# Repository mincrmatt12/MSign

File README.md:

# MSign

Code + designs for an LED sign display board powered by an STM32 and ESP8266. Make sure you clone the submodules.

## Organization

- `board`: schematics and PCB layout
- `stm`: STM32 firmware (drives the display)
- `stmboot`: STM32 bootloader
- `esp`: ESP8266 firmware (grabs information from the internet)
- `espweb`: ESP8266 web-based configuration page source
- `cfgserver`: Server for shipping unattended config and software updates (without using the webui)
- `bmap`: Tools for generating graphics resources
- `caplog`: Tools for debugging
- `vendor`: Various dependencies in source form (everything not listed below)
- `sim`: Stubs/shims for running the `esp` and `stm` codebases under linux.

## Dependencies

- A recent `arm-none-eabi-gcc` installation (suitably modern to deal with C++20; GCC 14 is what's tested)
- A `xtensa-lx106-elf-gcc` that can deal with C++20; preferably version 13.2.0 (which was available at one point in debian)
  - A suitable newlib/libstdc++ archive is available in `Dockerfile.build`
- Python 3 and the packages in `requirements.txt`
  - If you aren't building the `espweb` directory you do not require the `cryptography` package listed
- OpenOCD (for flashing)
  - If you have PlatformIO installed we use its OpenOCD by default, so you may not need to install it system-wide.
- CMake (version 3.13 or later is recommended)
- `quilt`, to apply the patches in `vendor` for the ESP8266 SDK

and everything checked out in the `vendor` directory. The ESP8266 SDK also usually requests you have python (specifically _system_ python, whatever runs from `python`) installed with it's requirements (`vendor/ESP8266_RTOS_SDK/requirements.txt`)

A Docker file with these is provided as `Dockerfile.build`.

For building the `espweb` you also need:

- yarn
- node 

A Docker file with _these_ is also provided as `Dockerfile.webbuild`

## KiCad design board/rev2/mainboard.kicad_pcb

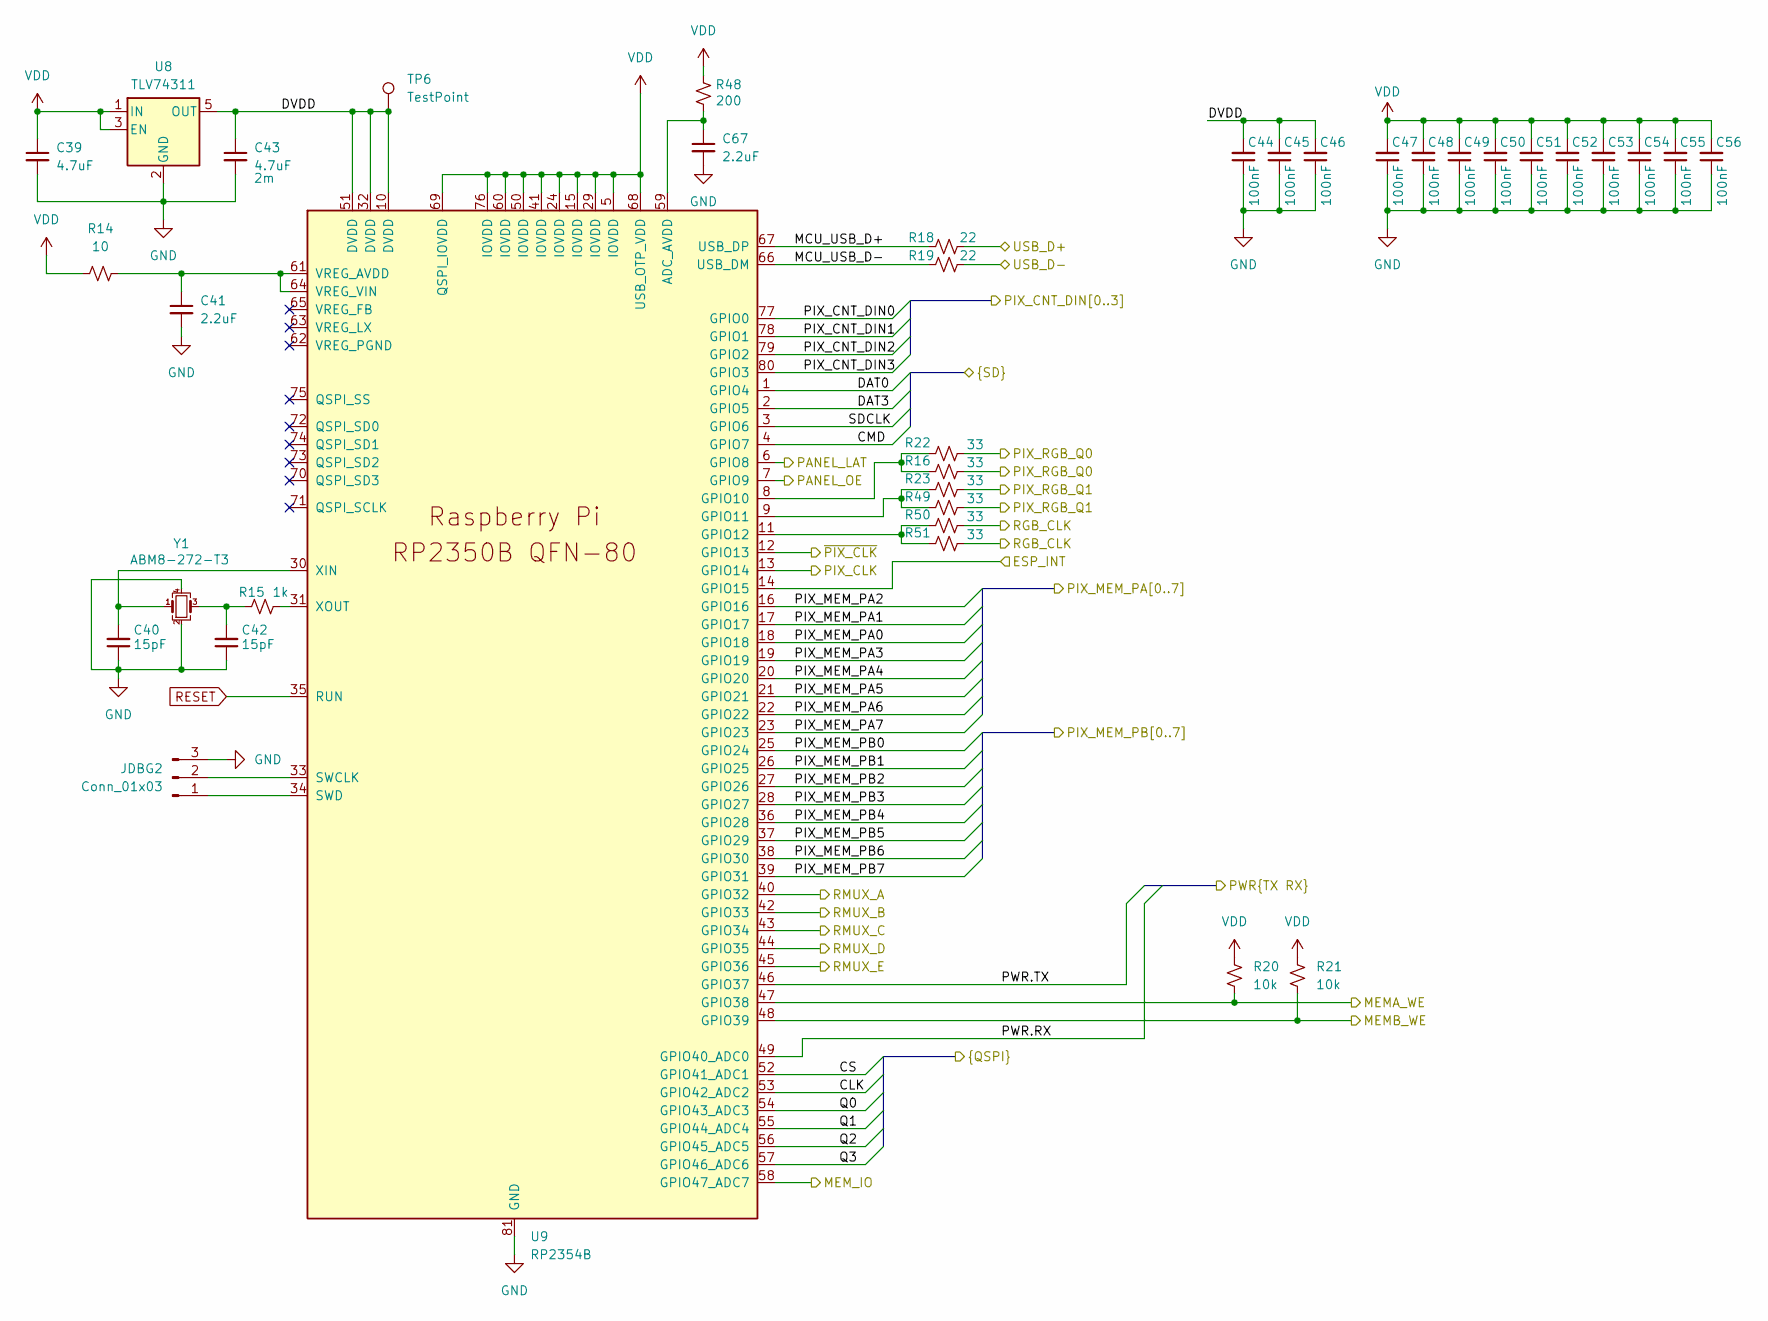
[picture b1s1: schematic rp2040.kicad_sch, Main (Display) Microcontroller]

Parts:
C39, C43: 4.7uF; C_1206_3216Metric; Part 1206B475K500NT; LCSC C29823
C40, C42: 15pF; C_0402_1005Metric; Part 0402CG150J500NT; LCSC C1548
C41, C67: 2.2uF; C_0603_1608Metric; Part CL10A225KO8NNNC; LCSC C23630
C44, C45, C46, C47, C48, C49, C50, C51, C52, C53, C54, C55, C56: 100nF; C_0402_1005Metric; Part CL05B104KB54PNC; LCSC C307331
JDBG2: Conn_01x03; PinHeader_1x03_P2.54mm_Vertical
R14: 10; R_0402_1005Metric; Part 0402WGF100JTCE; LCSC C25077
R15: 1k; R_0402_1005Metric; Part 0402WGF1001TCE; LCSC C11702
R16, R22, R23, R49, R50, R51: 33; R_0402_1005Metric; Part 0402WGF330JTCE; LCSC C25105
R18, R19: 22; R_0402_1005Metric; Part 0402WGF220JTCE; LCSC C25092
R20, R21: 10k; R_0402_1005Metric; Part 0402WGF1002TCE; LCSC C25744
R48: 200; R_0402_1005Metric; Part 0402WGF2000TCE; LCSC C25087
TP6: TestPoint; TestPoint_Pad_D1.0mm
U8: TLV74311; SOT-23-5; Part TLV74311PDBVR; LCSC C485147
U9: RP2354B; RP2350-QFN-80-1EP_10x10_P0.4mm_EP3.4x3.4mm_ThermalVias; Part RP2354B; LCSC C39843328
Y1: ABM8-272-T3; Crystal_SMD_3225-4Pin_3.2x2.5mm; Part ABM8-272-T3; LCSC C20625731

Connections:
/Decoder/MEMA_WE: R20.2, U9.47 (GPIO38); also elsewhere on the board
/Decoder/MEMB_WE: R21.2, U9.48 (GPIO39); also elsewhere on the board
/Decoder/MEM_IO: U9.58 (GPIO47_ADC7); also elsewhere on the board
/Decoder/Output Stage A/PIX_RGB_Q0: R16.2, R22.2; also elsewhere on the board
/Decoder/Output Stage A/PIX_RGB_Q1: R23.2, R49.2; also elsewhere on the board
/Decoder/PIX_CLK: U9.13 (GPIO14); also elsewhere on the board
/Decoder/PIX_CNT_DIN0: U9.77 (GPIO0); also elsewhere on the board
/Decoder/PIX_CNT_DIN1: U9.78 (GPIO1); also elsewhere on the board
/Decoder/PIX_CNT_DIN2: U9.79 (GPIO2); also elsewhere on the board
/Decoder/PIX_CNT_DIN3: U9.80 (GPIO3); also elsewhere on the board
/Decoder/PIX_MEM_PA0: U9.25 (GPIO24); also elsewhere on the board
/Decoder/PIX_MEM_PA1: U9.26 (GPIO25); also elsewhere on the board
/Decoder/PIX_MEM_PA2: U9.27 (GPIO26); also elsewhere on the board
/Decoder/PIX_MEM_PA3: U9.28 (GPIO27); also elsewhere on the board
/Decoder/PIX_MEM_PA4: U9.36 (GPIO28); also elsewhere on the board
/Decoder/PIX_MEM_PA5: U9.37 (GPIO29); also elsewhere on the board
/Decoder/PIX_MEM_PA6: U9.38 (GPIO30); also elsewhere on the board
/Decoder/PIX_MEM_PA7: U9.39 (GPIO31); also elsewhere on the board
/Decoder/PIX_MEM_PB0: U9.18 (GPIO18); also elsewhere on the board
/Decoder/PIX_MEM_PB1: U9.17 (GPIO17); also elsewhere on the board
/Decoder/PIX_MEM_PB2: U9.16 (GPIO16); also elsewhere on the board
/Decoder/PIX_MEM_PB3: U9.19 (GPIO19); also elsewhere on the board
/Decoder/PIX_MEM_PB4: U9.20 (GPIO20); also elsewhere on the board
/Decoder/PIX_MEM_PB5: U9.21 (GPIO21); also elsewhere on the board
/Decoder/PIX_MEM_PB6: U9.22 (GPIO22); also elsewhere on the board
/Decoder/PIX_MEM_PB7: U9.23 (GPIO23); also elsewhere on the board
/Decoder/RGB_CLK: R50.2, R51.2; also elsewhere on the board
/Display MCU/CLK: U9.53 (GPIO42_ADC2); also elsewhere on the board
/Display MCU/CMD: U9.4 (GPIO7); also elsewhere on the board
/Display MCU/CS: U9.52 (GPIO41_ADC1); also elsewhere on the board
/Display MCU/DAT0: U9.1 (GPIO4); also elsewhere on the board
/Display MCU/DAT3: U9.2 (GPIO5); also elsewhere on the board
/Display MCU/DVDD: C43.1, C44.2, C45.2, C46.2, TP6.1 (1_1), U8.5 (OUT), U9.10 (DVDD), U9.32 (DVDD), U9.51 (DVDD)
/Display MCU/ESP_INT: U9.14 (GPIO15); also elsewhere on the board
/Display MCU/MCU_USB_D+: R18.1, U9.67 (USB_DP)
/Display MCU/MCU_USB_D-: R19.1, U9.66 (USB_DM)
/Display MCU/PANEL_LAT: U9.6 (GPIO8); also elsewhere on the board
/Display MCU/PANEL_OE: U9.7 (GPIO9); also elsewhere on the board
/Display MCU/PWR.RX: U9.49 (GPIO40_ADC0); also elsewhere on the board
/Display MCU/PWR.TX: U9.46 (GPIO37); also elsewhere on the board
/Display MCU/Q0: U9.54 (GPIO43_ADC3); also elsewhere on the board
/Display MCU/Q1: U9.55 (GPIO44_ADC4); also elsewhere on the board
/Display MCU/Q2: U9.56 (GPIO45_ADC5); also elsewhere on the board
/Display MCU/Q3: U9.57 (GPIO46_ADC6); also elsewhere on the board
/Display MCU/RMUX_A: U9.40 (GPIO32); also elsewhere on the board
/Display MCU/RMUX_B: U9.42 (GPIO33); also elsewhere on the board
/Display MCU/RMUX_C: U9.43 (GPIO34); also elsewhere on the board
/Display MCU/RMUX_D: U9.44 (GPIO35); also elsewhere on the board
/Display MCU/RMUX_E: U9.45 (GPIO36); also elsewhere on the board
/Display MCU/SDCLK: U9.3 (GPIO6); also elsewhere on the board
/Display MCU/USB_D+: R18.2; also elsewhere on the board
/Display MCU/USB_D-: R19.2; also elsewhere on the board
/Display MCU/~PIX_CLK: U9.12 (GPIO13); also elsewhere on the board
GND: C39.2, C40.1, C41.2, C42.1, C43.2, C44.1, C45.1, C46.1, C47.1, C48.1, C49.1, C50.1, C51.1, C52.1, C53.1, C54.1, C55.1, C56.1, C67.2, JDBG2.3, U8.2 (GND), U9.81 (GND), Y1.2, Y1.4; also elsewhere on the board
unnamed: C42.2, R15.1, Y1.3
unnamed: JDBG2.1, U9.34 (SWD)
unnamed: JDBG2.2, U9.33 (SWCLK)
unnamed: C67.1, R48.2, U9.59 (ADC_AVDD)
unnamed: R16.1, R22.1, U9.8 (GPIO10)
unnamed: R23.1, R49.1, U9.9 (GPIO11)
unnamed: R50.1, R51.1, U9.11 (GPIO12)
unnamed: C41.1, R14.2, U9.61 (VREG_AVDD), U9.64 (VREG_VIN)
unnamed: C40.2, U9.30 (XIN), Y1.1
unnamed: R15.2, U9.31 (XOUT)
RESET: U9.35 (RUN); also elsewhere on the board
VDD: C39.1, C47.2, C48.2, C49.2, C50.2, C51.2, C52.2, C53.2, C54.2, C55.2, C56.2, R14.1, R20.1, R21.1, R48.1, U8.1 (IN), U8.3 (EN), U9.5 (IOVDD), U9.15 (IOVDD), U9.24 (IOVDD), U9.29 (IOVDD), U9.41 (IOVDD), U9.50 (IOVDD), U9.60 (IOVDD), U9.68 (USB_OTP_VDD), U9.69 (QSPI_IOVDD), U9.76 (IOVDD); also elsewhere on the board

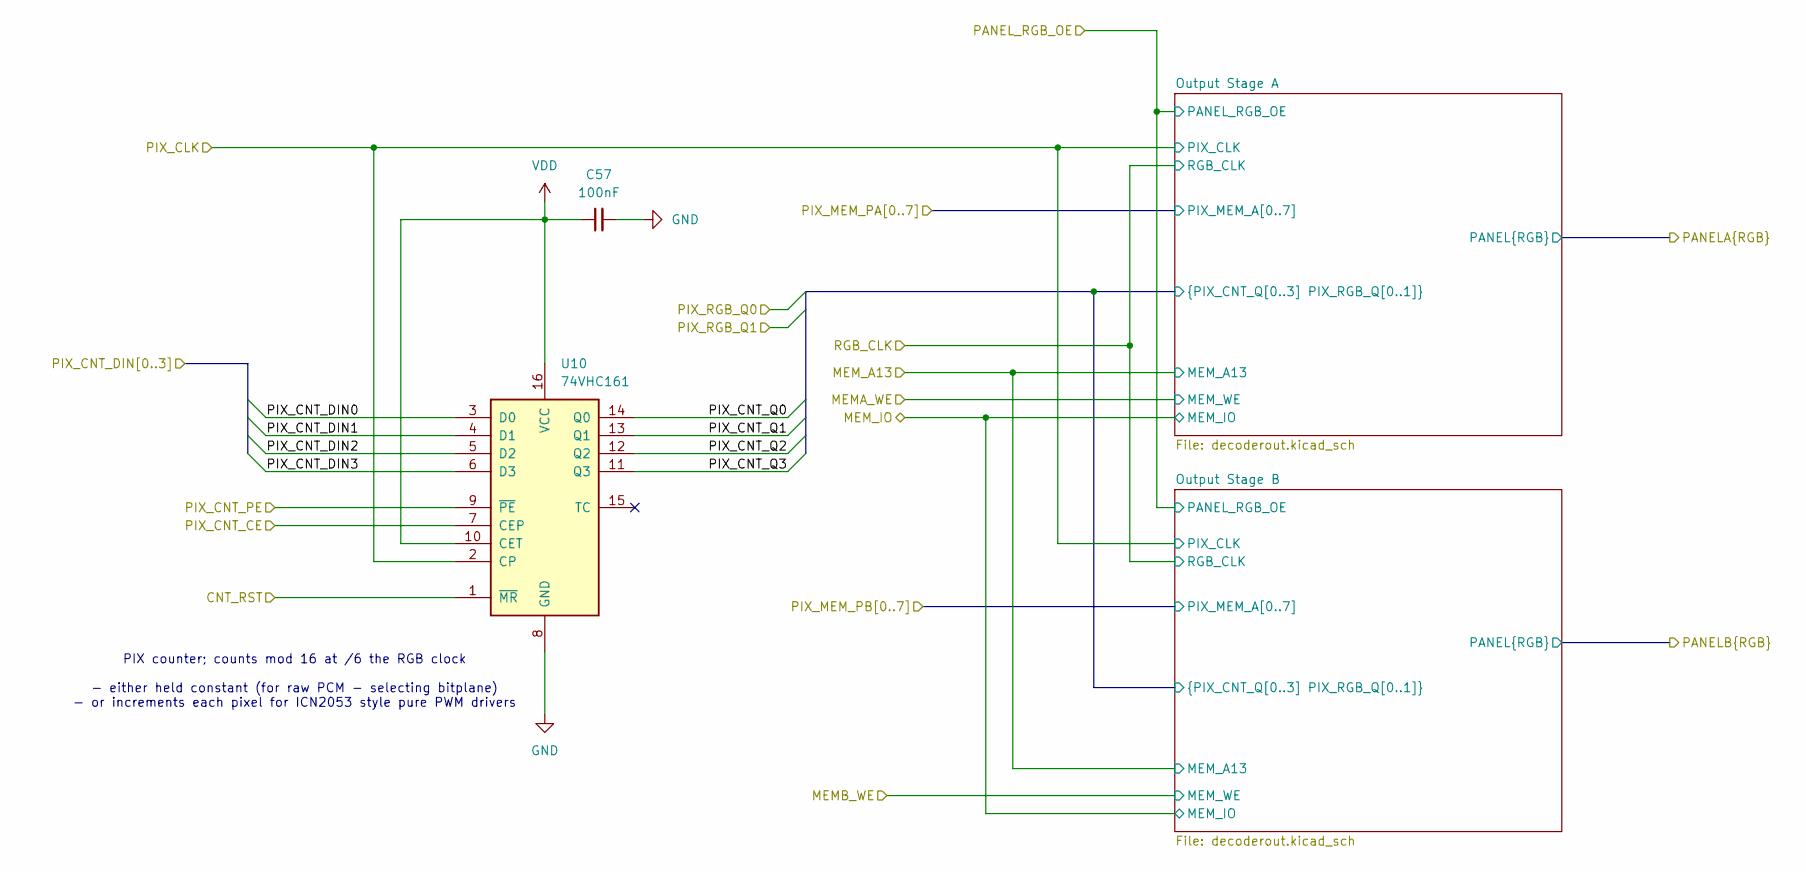
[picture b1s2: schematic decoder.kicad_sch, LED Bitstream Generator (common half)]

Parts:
C57: 100nF; C_0402_1005Metric; Part CL05B104KB54PNC; LCSC C307331
U10: 74VHC161; TSSOP-16_4.4x5mm_P0.65mm; Part 74VHC161FT(BJ); LCSC C7421276

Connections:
/Decoder/CNT_RST: U10.1 (~MR); also elsewhere on the board
/Decoder/Output Stage A/PIX_CNT_Q0: U10.14 (Q0); also elsewhere on the board
/Decoder/Output Stage A/PIX_CNT_Q1: U10.13 (Q1); also elsewhere on the board
/Decoder/Output Stage A/PIX_CNT_Q2: U10.12 (Q2); also elsewhere on the board
/Decoder/Output Stage A/PIX_CNT_Q3: U10.11 (Q3); also elsewhere on the board
/Decoder/PIX_CLK: U10.2 (CP); also elsewhere on the board
/Decoder/PIX_CNT_CE: U10.7 (CEP); also elsewhere on the board
/Decoder/PIX_CNT_DIN0: U10.3 (D0); also elsewhere on the board
/Decoder/PIX_CNT_DIN1: U10.4 (D1); also elsewhere on the board
/Decoder/PIX_CNT_DIN2: U10.5 (D2); also elsewhere on the board
/Decoder/PIX_CNT_DIN3: U10.6 (D3); also elsewhere on the board
/Decoder/PIX_CNT_PE: U10.9 (~PE); also elsewhere on the board
GND: C57.2, U10.8 (GND); also elsewhere on the board
VDD: C57.1, U10.10 (CET), U10.16 (VCC); also elsewhere on the board

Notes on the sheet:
PIX counter; counts mod 16 at /6 the RGB clock - either held constant (for raw PCM - selecting bitplane) - or increments each pixel for ICN2053 style pure PWM drivers

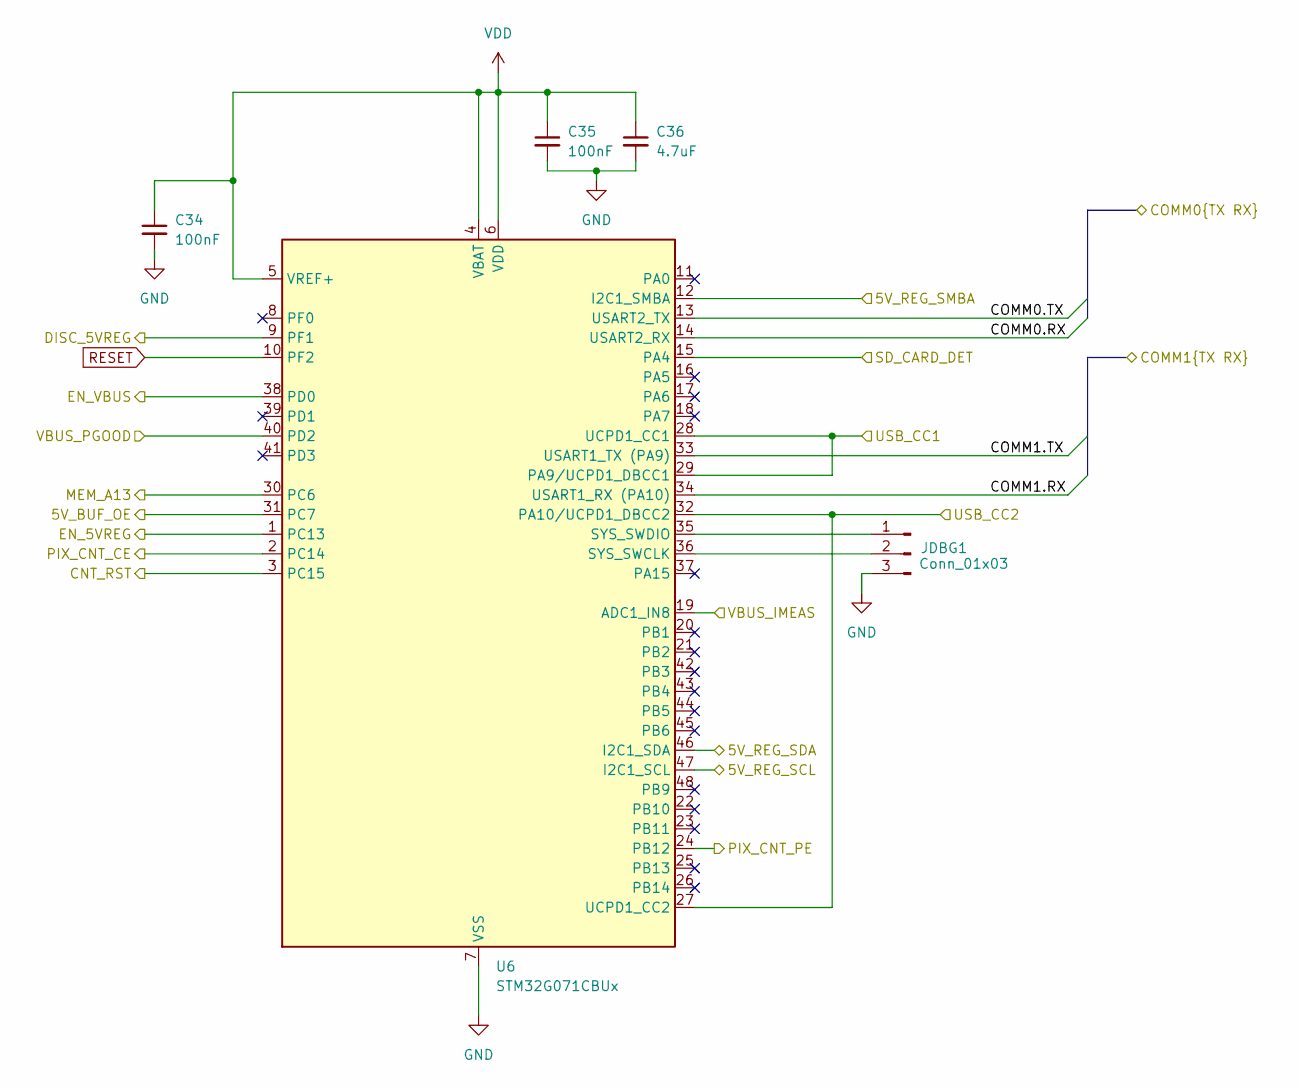
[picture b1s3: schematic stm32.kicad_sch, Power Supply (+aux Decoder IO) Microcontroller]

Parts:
C34, C35: 100nF; C_0402_1005Metric; Part CL05B104KB54PNC; LCSC C307331
C36: 4.7uF; C_1206_3216Metric; Part 1206B475K500NT; LCSC C29823
JDBG1: Conn_01x03; PinHeader_1x03_P2.54mm_Vertical
U6: STM32G071CBUx; QFN-48-1EP_7x7mm_P0.5mm_EP5.6x5.6mm; Part STM32G071CBU6; LCSC C529343

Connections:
/Decoder/CNT_RST: U6.3 (PC15); also elsewhere on the board
/Decoder/MEM_A13: U6.30 (PC6); also elsewhere on the board
/Decoder/PANEL_RGB_OE: U6.31 (PC7); also elsewhere on the board
/Decoder/PIX_CNT_CE: U6.2 (PC14); also elsewhere on the board
/Decoder/PIX_CNT_PE: U6.24 (PB12); also elsewhere on the board
/Display MCU/DET: U6.15 (PA4); also elsewhere on the board
/Display MCU/PWR.RX: U6.14 (USART2_RX); also elsewhere on the board
/Display MCU/PWR.TX: U6.13 (USART2_TX); also elsewhere on the board
/Power MCU/5V_REG_SCL: U6.47 (I2C1_SCL); also elsewhere on the board
/Power MCU/5V_REG_SDA: U6.46 (I2C1_SDA); also elsewhere on the board
/Power MCU/5V_REG_SMBA: U6.12 (I2C1_SMBA); also elsewhere on the board
/Power MCU/COMM1.RX: U6.34 (USART1_RX (PA10)); also elsewhere on the board
/Power MCU/COMM1.TX: U6.33 (USART1_TX (PA9)); also elsewhere on the board
/Power MCU/DISC_5VREG: U6.9 (PF1); also elsewhere on the board
/Power MCU/EN_5VREG: U6.1 (PC13); also elsewhere on the board
/Power MCU/EN_VBUS: U6.38 (PD0); also elsewhere on the board
/Power MCU/USB_CC1: U6.28 (UCPD1_CC1), U6.29 (PA9/UCPD1_DBCC1); also elsewhere on the board
/Power MCU/USB_CC2: U6.27 (UCPD1_CC2), U6.32 (PA10/UCPD1_DBCC2); also elsewhere on the board
/Power MCU/VBUS_IMEAS: U6.19 (ADC1_IN8); also elsewhere on the board
/Power MCU/VBUS_PGOOD: U6.40 (PD2); also elsewhere on the board
GND: C34.2, C35.2, C36.2, JDBG1.3, U6.7 (VSS), U6.49 (VSS); also elsewhere on the board
unnamed: JDBG1.1, U6.35 (SYS_SWDIO)
unnamed: JDBG1.2, U6.36 (SYS_SWCLK)
RESET: U6.10 (PF2); also elsewhere on the board
VDD: C34.1, C35.1, C36.1, U6.4 (VBAT), U6.5 (VREF+), U6.6 (VDD); also elsewhere on the board

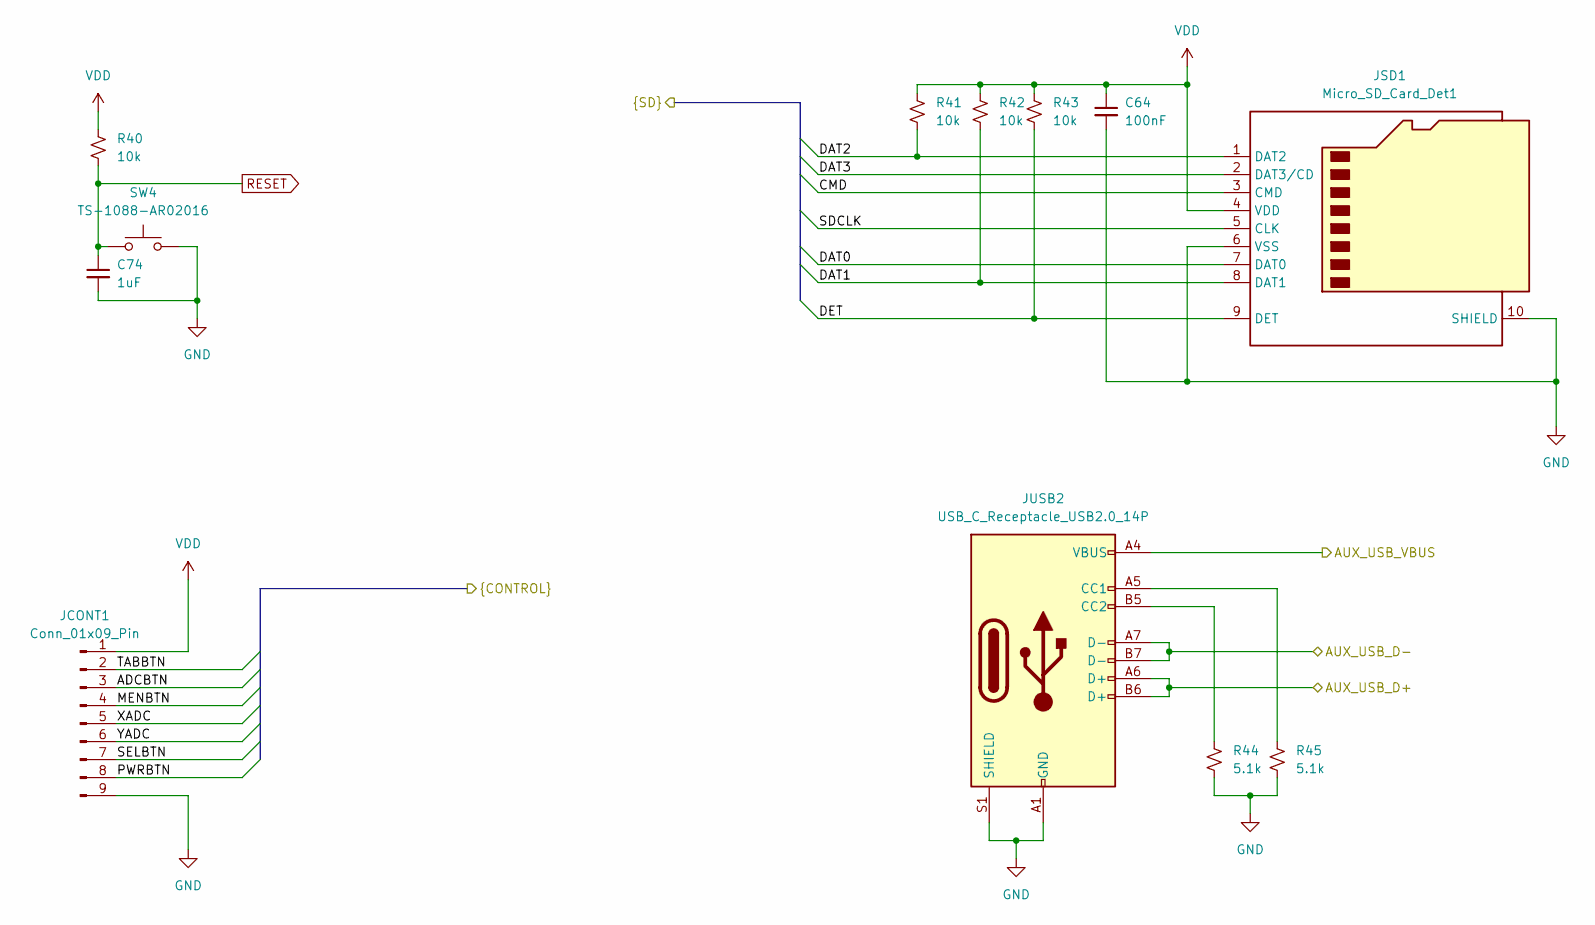
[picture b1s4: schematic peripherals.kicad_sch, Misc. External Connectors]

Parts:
C64: 100nF; C_0402_1005Metric; Part CL05B104KB54PNC; LCSC C307331
C74: 1uF; C_0603_1608Metric; Part CL10A105KB8NNNC; LCSC C15849
JCONT1: Conn_01x09_Pin; PinHeader_1x09_P2.54mm_Horizontal
JSD1: Micro_SD_Card_Det1; microSD_XUNPU_TF-115-BCP9; Part TF-115-BCP9; LCSC C720505
JUSB2: USB_C_Receptacle_USB2.0_14P; USB_C_Receptacle_HRO_TYPE-C-31-M-12; Part TYPE-C-31-M-12; LCSC C165948
R40, R41, R42, R43: 10k; R_0805_2012Metric; Part 0805W8F1002T5E; LCSC C17414
R44, R45: 5.1k; R_0603_1608Metric; Part 0603WAF5101T5E; LCSC C23186
SW4: TS-1088-AR02016; SW_SPST_TS-1088-xR020; Part TS-1088-AR02016; LCSC C720477

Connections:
/Display MCU/CMD: JSD1.3 (CMD); also elsewhere on the board
/Display MCU/DAT0: JSD1.7 (DAT0); also elsewhere on the board
/Display MCU/DAT1: JSD1.8 (DAT1), R42.2
/Display MCU/DAT2: JSD1.1 (DAT2), R41.2
/Display MCU/DAT3: JSD1.2 (DAT3/CD); also elsewhere on the board
/Display MCU/DET: JSD1.9 (DET), R43.2; also elsewhere on the board
/Display MCU/SDCLK: JSD1.5 (CLK); also elsewhere on the board
/Peripherals/ADCBTN: JCONT1.3; also elsewhere on the board
/Peripherals/AUX_USB_D+: JUSB2.A6 (D+), JUSB2.B6 (D+); also elsewhere on the board
/Peripherals/AUX_USB_D-: JUSB2.A7 (D-), JUSB2.B7 (D-); also elsewhere on the board
/Peripherals/AUX_USB_VBUS: JUSB2.A4 (VBUS), JUSB2.A9 (VBUS), JUSB2.B4 (VBUS), JUSB2.B9 (VBUS); also elsewhere on the board
/Peripherals/MENBTN: JCONT1.4; also elsewhere on the board
/Peripherals/PWRBTN: JCONT1.8; also elsewhere on the board
/Peripherals/SELBTN: JCONT1.7; also elsewhere on the board
/Peripherals/TABBTN: JCONT1.2; also elsewhere on the board
/Peripherals/XADC: JCONT1.5; also elsewhere on the board
/Peripherals/YADC: JCONT1.6; also elsewhere on the board
GND: C64.2, C74.2, JCONT1.9, JSD1.6 (VSS), JSD1.10 (SHIELD), JUSB2.A1 (GND), JUSB2.A12 (GND), JUSB2.B1 (GND), JUSB2.B12 (GND), JUSB2.S1 (SHIELD), R44.2, R45.2, SW4.2; also elsewhere on the board
unnamed: JUSB2.A5 (CC1), R45.1
unnamed: JUSB2.B5 (CC2), R44.1
RESET: C74.1, R40.2, SW4.1; also elsewhere on the board
VDD: C64.1, JCONT1.1, JSD1.4 (VDD), R40.1, R41.1, R42.1, R43.1; also elsewhere on the board

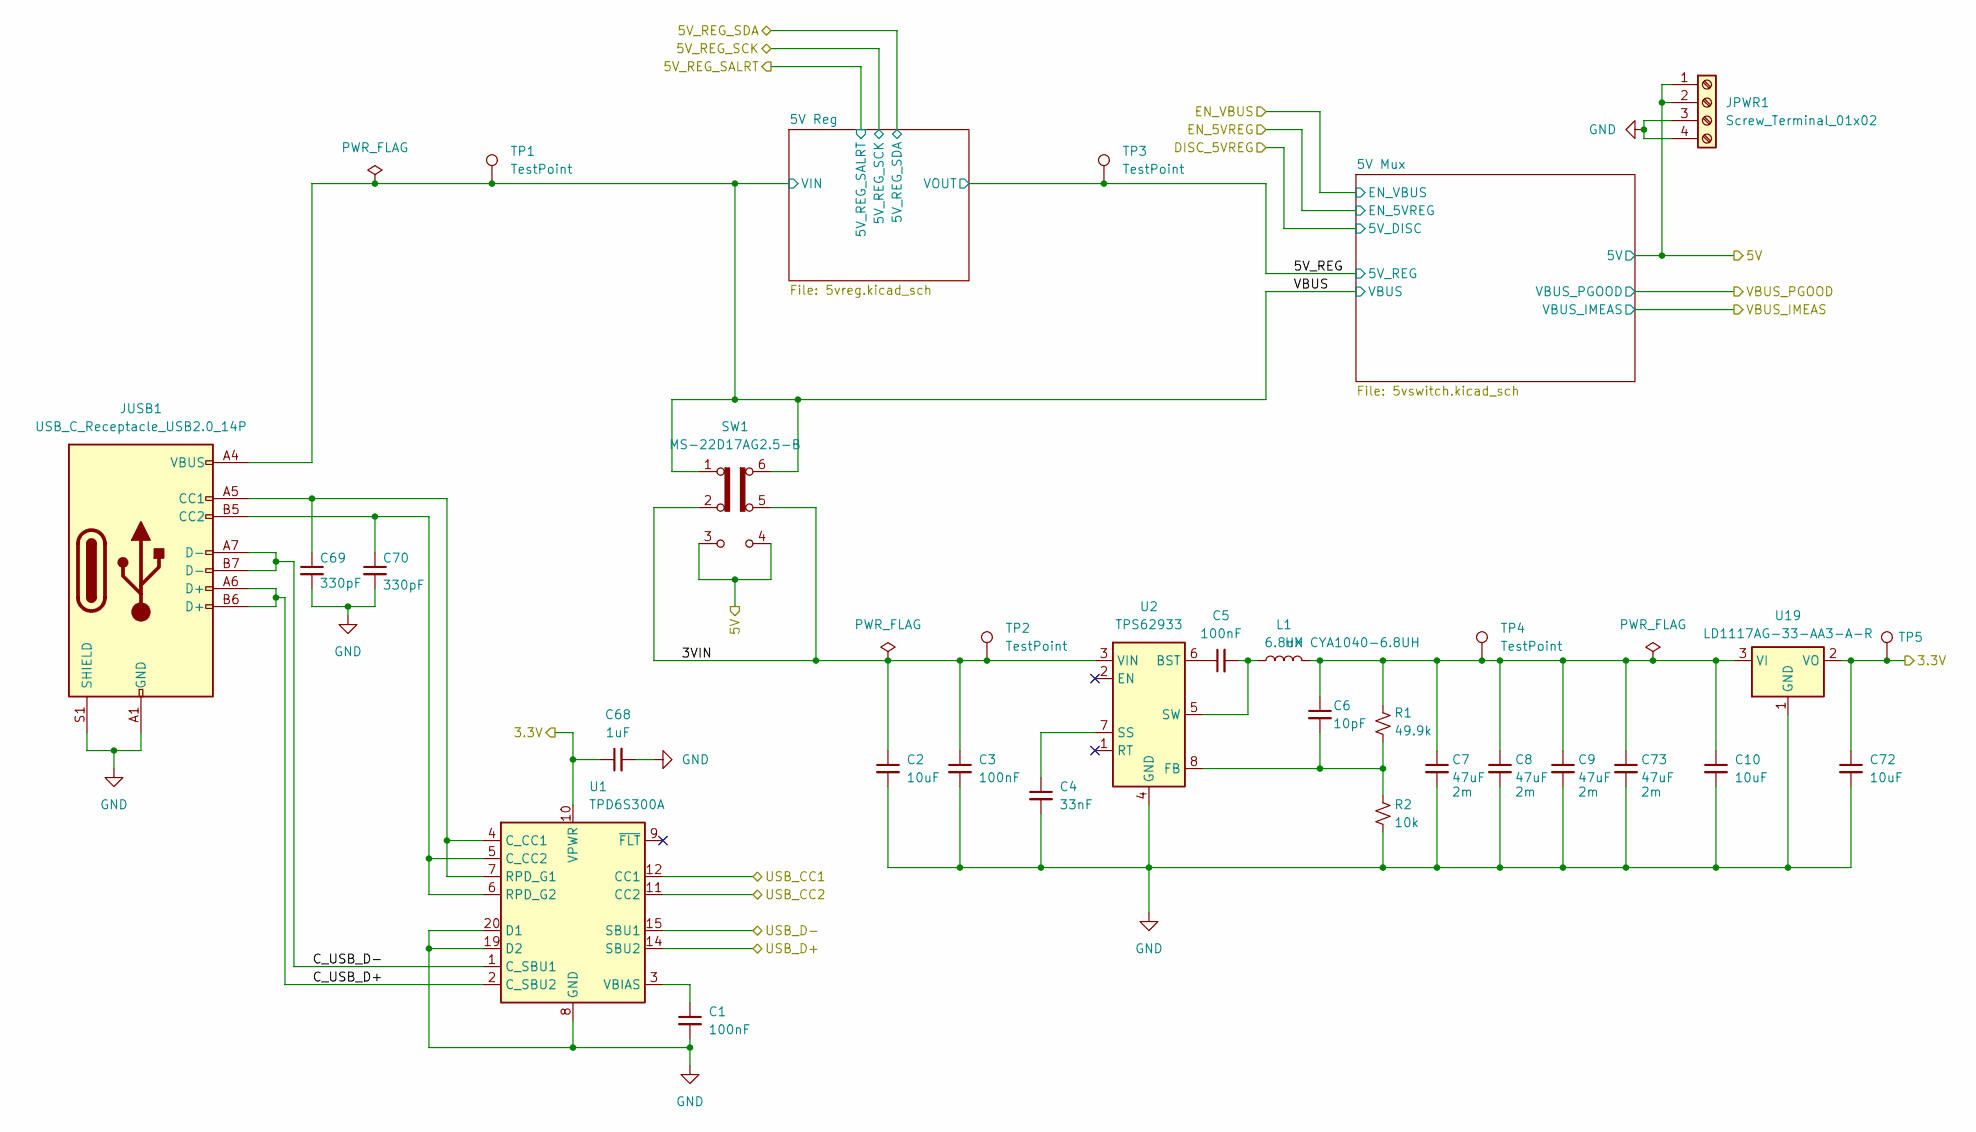
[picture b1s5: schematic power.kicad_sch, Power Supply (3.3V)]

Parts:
C1, C3, C5: 100nF; C_0402_1005Metric; Part CL05B104KB54PNC; LCSC C307331
C2, C10, C72: 10uF; C_1206_3216Metric; Part CL31A106KBHNNNE; LCSC C13585
C4: 33nF; C_0603_1608Metric; Part CL10B333KB8NNNC; LCSC C21117
C6: 10pF; C_0402_1005Metric; Part CL05C100JB5NNNC; LCSC C32949
C7, C8, C9, C73: 47uF; C_1206_3216Metric; Part CL31A476MPHNNNE; LCSC C96123
C68: 1uF; C_0603_1608Metric; Part CL10A105KB8NNNC; LCSC C15849
C69, C70: 330pF; C_0603_1608Metric; Part CL10C331JB8NNNC; LCSC C1664
JPWR1: Screw_Terminal_01x02; CONN-TH_4P-P9.50_WJHB9500M-9.5-04P-13-00A
JUSB1: USB_C_Receptacle_USB2.0_14P; USB_C_Receptacle_HRO_TYPE-C-31-M-12; Part TYPE-C-31-M-12; LCSC C165948
L1: 6.8uH; L_Chilisin_BMRF00101040; Part HX CYA1040-6.8UH; LCSC C7502775
R1: 49.9k; R_0603_1608Metric; Part 0603WAF4992T5E; LCSC C23184
R2: 10k; R_0402_1005Metric; Part 0402WGF1002TCE; LCSC C25744
SW1: MS-22D17AG2.5-B; SW-SMD_MS-22D17AG2.5; Part MS-22D17AG2.5-B; LCSC C20611671
TP1, TP2, TP3, TP4, TP5: TestPoint; TestPoint_Pad_D1.0mm
U1: TPD6S300A; WQFN-20-1EP_3x3mm_P0.4mm_EP1.7x1.7mm_ThermalVias; Part TPD6S300ARUKR; LCSC C2876380
U2: TPS62933; SOT-583-8; Part TPS62933DRLR; LCSC C3200405
U19: LD1117AG-33-AA3-A-R; SOT-223-3_TabPin2; Part LD1117AG-33-AA3-A-R; LCSC C71121

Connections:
+5V: JPWR1.1, JPWR1.2, SW1.3 (C), SW1.4 (A); also elsewhere on the board
/Power MCU/USB_CC1: U1.12 (CC1); also elsewhere on the board
/Power MCU/USB_CC2: U1.11 (CC2); also elsewhere on the board
/Power/3VIN: C2.1, C3.1, SW1.2 (B), SW1.5 (B), TP2.1 (1_1), U2.3 (VIN)
/Power/5V_REG: TP3.1 (1_1); also elsewhere on the board
/Power/C_USB_D+: JUSB1.A6 (D+), JUSB1.B6 (D+), U1.2 (C_SBU2)
/Power/C_USB_D-: JUSB1.A7 (D-), JUSB1.B7 (D-), U1.1 (C_SBU1)
/Power/USB_D+: U1.14 (SBU2); also elsewhere on the board
/Power/USB_D-: U1.15 (SBU1); also elsewhere on the board
/Power/VBUS: JUSB1.A4 (VBUS), JUSB1.A9 (VBUS), JUSB1.B4 (VBUS), JUSB1.B9 (VBUS), SW1.1 (A), SW1.6 (C), TP1.1 (1_1); also elsewhere on the board
GND: C1.2, C2.2, C3.2, C4.2, C7.2, C8.2, C9.2, C10.2, C68.2, C69.2, C70.2, C72.2, C73.2, JPWR1.3, JPWR1.4, JUSB1.A1 (GND), JUSB1.A12 (GND), JUSB1.B1 (GND), JUSB1.B12 (GND), JUSB1.S1 (SHIELD), R2.2, U1.8 (GND), U1.13 (GND), U1.16 (GND), U1.17 (GND), U1.18 (GND), U1.19 (D2), U1.20 (D1), U1.21 (GND), U2.4 (GND), U19.1 (GND); also elsewhere on the board
unnamed: C69.1, JUSB1.A5 (CC1), U1.4 (C_CC1), U1.7 (RPD_G1)
unnamed: C70.1, JUSB1.B5 (CC2), U1.5 (C_CC2), U1.6 (RPD_G2)
unnamed: C1.1, U1.3 (VBIAS)
unnamed: C5.1, U2.6 (BST)
unnamed: C6.2, R1.2, R2.1, U2.8 (FB)
unnamed: C4.1, U2.7 (SS)
unnamed: C5.2, L1.1, U2.5 (SW)
unnamed: C6.1, C7.1, C8.1, C9.1, C10.1, C73.1, L1.2, R1.1, TP4.1 (1_1), U19.3 (VI)
VDD: C68.1, C72.1, TP5.1 (1_1), U1.10 (VPWR), U19.2 (VO); also elsewhere on the board

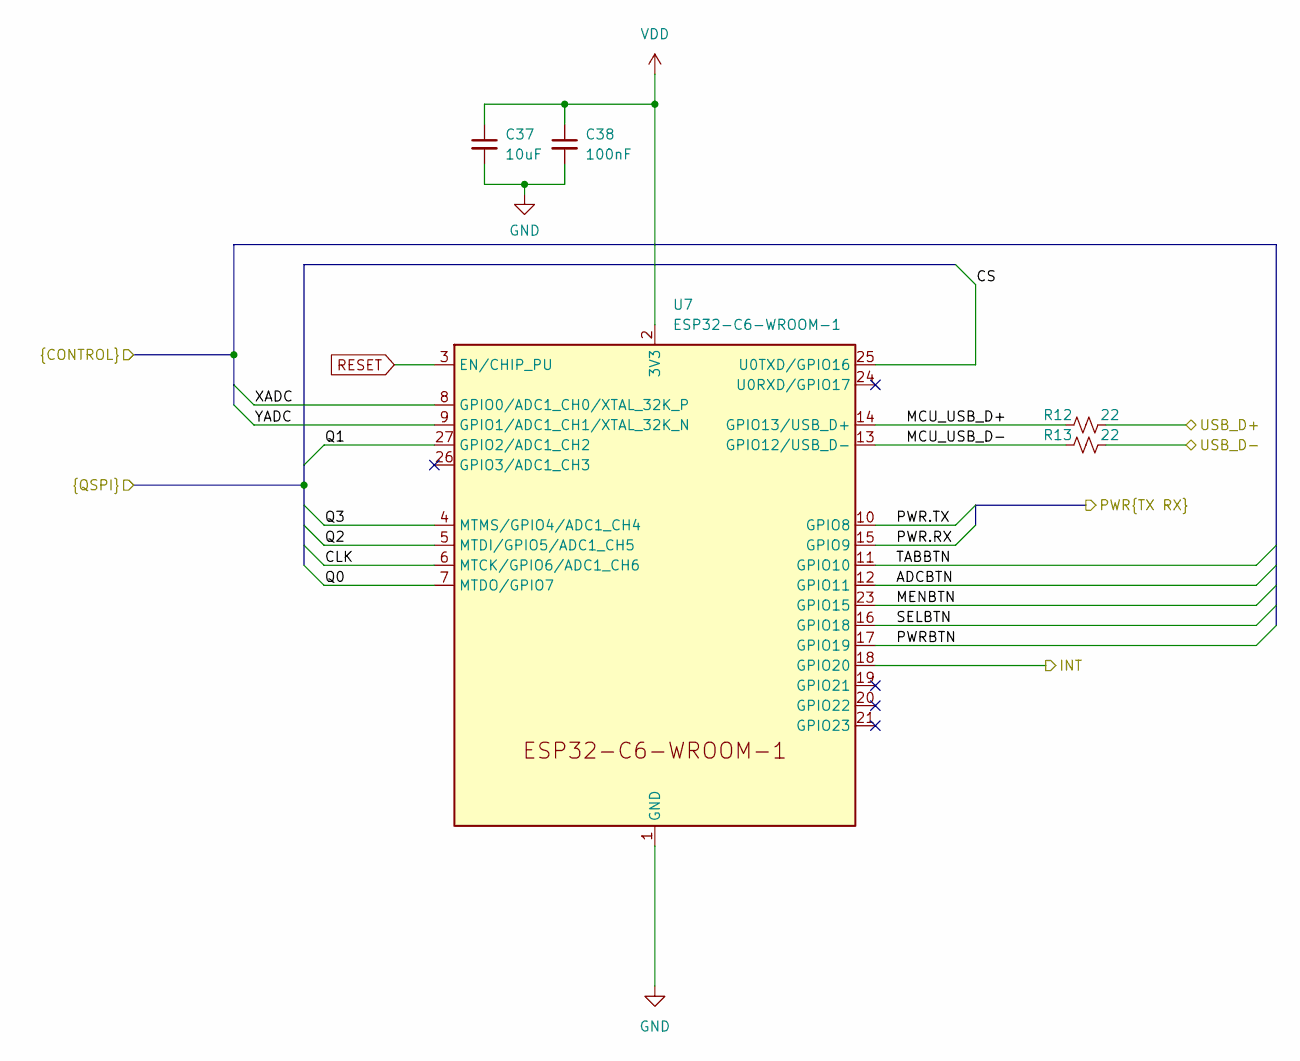
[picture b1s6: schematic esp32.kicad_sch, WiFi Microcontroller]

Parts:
C37: 10uF; C_1206_3216Metric; Part CL31A106KBHNNNE; LCSC C13585
C38: 100nF; C_0402_1005Metric; Part CL05B104KB54PNC; LCSC C307331
R12, R13: 22; R_0402_1005Metric; Part 0402WGF220JTCE; LCSC C25092
U7: ESP32-C6-WROOM-1; Part ESP32-C6-WROOM-1-N8; LCSC C5366877

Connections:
/Display MCU/CLK: U7.6 (MTCK/GPIO6/ADC1_CH6); also elsewhere on the board
/Display MCU/CS: U7.25 (U0TXD/GPIO16); also elsewhere on the board
/Display MCU/ESP_INT: U7.18 (GPIO20); also elsewhere on the board
/Display MCU/Q0: U7.7 (MTDO/GPIO7); also elsewhere on the board
/Display MCU/Q1: U7.27 (GPIO2/ADC1_CH2); also elsewhere on the board
/Display MCU/Q2: U7.5 (MTDI/GPIO5/ADC1_CH5); also elsewhere on the board
/Display MCU/Q3: U7.4 (MTMS/GPIO4/ADC1_CH4); also elsewhere on the board
/Peripherals/ADCBTN: U7.12 (GPIO11); also elsewhere on the board
/Peripherals/MENBTN: U7.23 (GPIO15); also elsewhere on the board
/Peripherals/PWRBTN: U7.17 (GPIO19); also elsewhere on the board
/Peripherals/SELBTN: U7.16 (GPIO18); also elsewhere on the board
/Peripherals/TABBTN: U7.11 (GPIO10); also elsewhere on the board
/Peripherals/XADC: U7.8 (GPIO0/ADC1_CH0/XTAL_32K_P); also elsewhere on the board
/Peripherals/YADC: U7.9 (GPIO1/ADC1_CH1/XTAL_32K_N); also elsewhere on the board
/Power MCU/COMM1.RX: U7.15 (GPIO9); also elsewhere on the board
/Power MCU/COMM1.TX: U7.10 (GPIO8); also elsewhere on the board
/USB Mux/ESP_D+: R12.2; also elsewhere on the board
/USB Mux/ESP_D-: R13.2; also elsewhere on the board
/WiFi MCU/MCU_USB_D+: R12.1, U7.14 (GPIO13/USB_D+)
/WiFi MCU/MCU_USB_D-: R13.1, U7.13 (GPIO12/USB_D-)
GND: C37.2, C38.2, U7.1 (GND), U7.28 (GND), U7.29 (GND); also elsewhere on the board
RESET: U7.3 (EN/CHIP_PU); also elsewhere on the board
VDD: C37.1, C38.1, U7.2 (3V3); also elsewhere on the board
